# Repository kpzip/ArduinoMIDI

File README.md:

# ArduinoMIDI
program for playing MIDI files from an Arduino microcontroller automatically

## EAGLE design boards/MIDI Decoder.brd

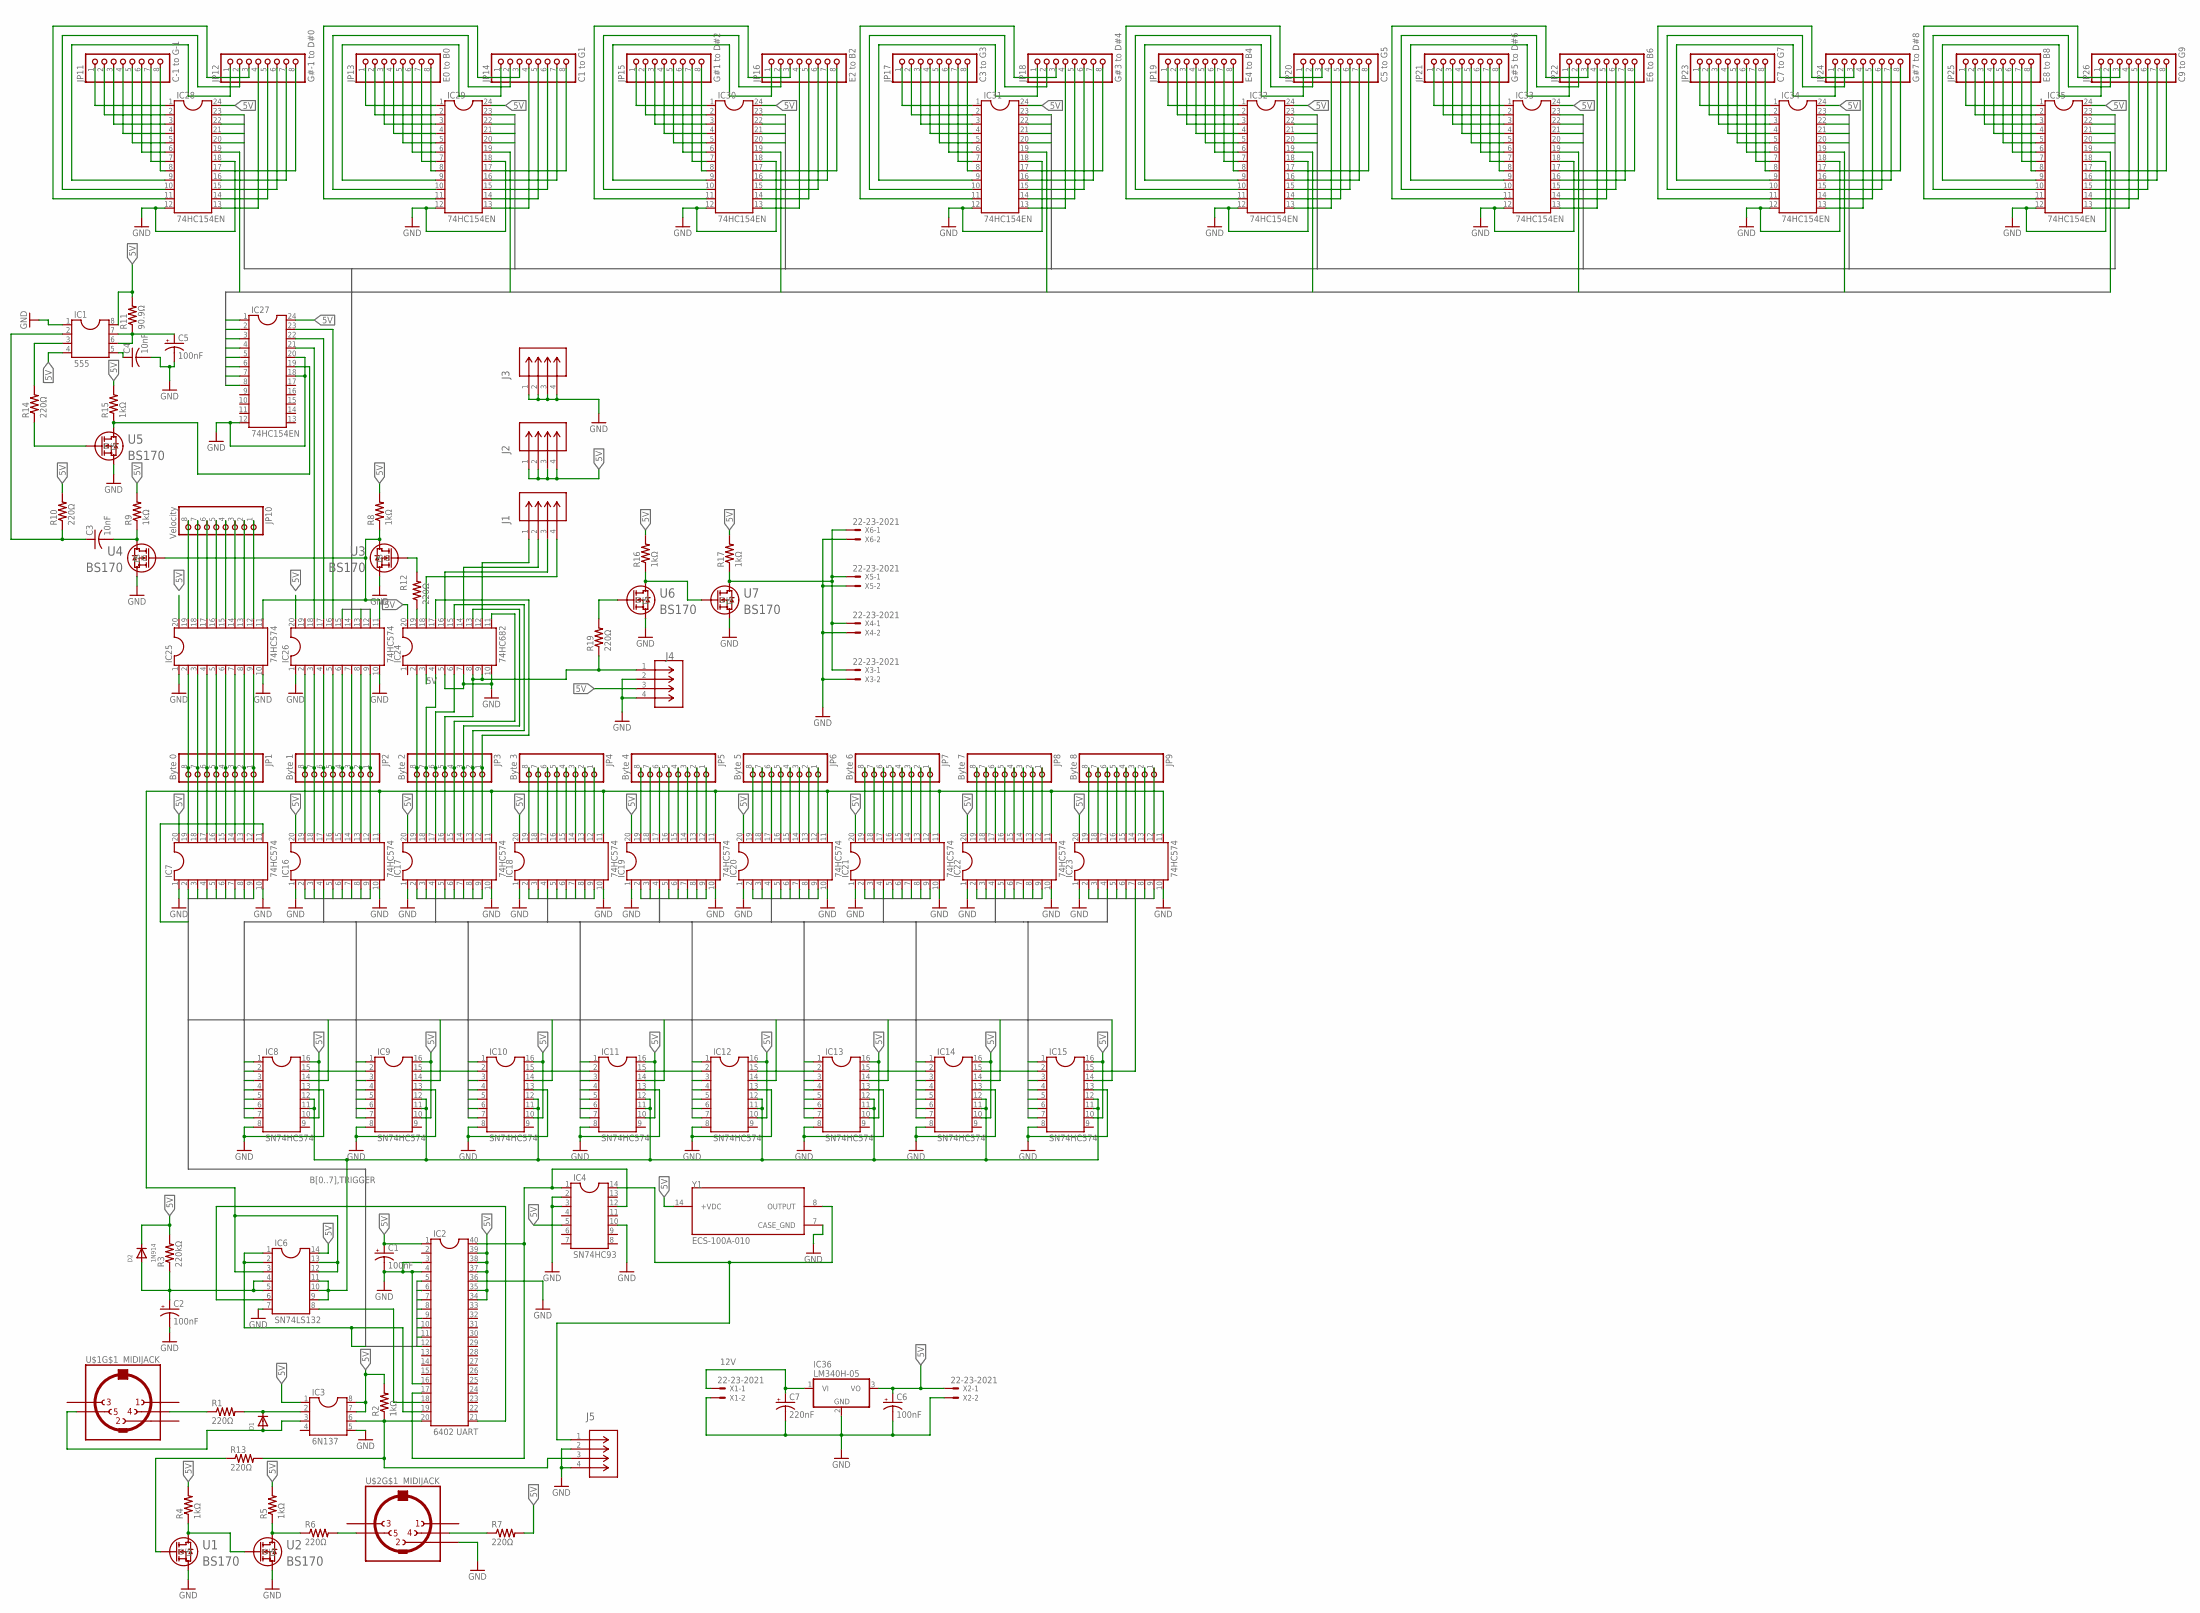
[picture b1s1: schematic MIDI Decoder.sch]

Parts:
C1, C2, C5, C6: 100nF; E1,8-4
C3, C4: 10nF; C050-025X075
C7: 220nF; E2-5
D1: DIODEDO-1N4148; DO-1N4148
D2: 1N914; DO-1N4148
IC1: 555; SOCKET-08
IC2: 6402 UART; SOCKET-40
IC3: 6N137; SOCKET-08
IC4: SN74HC93; SOCKET-14
IC6: SN74LS132; SOCKET-14
IC7, IC16, IC17, IC18, IC19, IC20, IC21, IC22, IC23, IC25, IC26: 74HC574; SOCKET-20
IC8, IC9, IC10, IC11, IC12, IC13, IC14, IC15: SN74HC574; SOCKET-16
IC24: 74HC682; SOCKET-20
IC27, IC28, IC29, IC30, IC31, IC32, IC33, IC34, IC35: 74HC154EN; SOCKET-24S
IC36: LM340H-05; TO220H
J1, J2, J3, J4, J5: 61300411121; CONN_61300411121_WRE
JP1: Byte 0; 1X08-BIG
JP2: Byte 1; 1X08-BIG
JP3: Byte 2; 1X08-BIG
JP4: Byte 3; 1X08-BIG
JP5: Byte 4; 1X08-BIG
JP6: Byte 5; 1X08-BIG
JP7: Byte 6; 1X08-BIG
JP8: Byte 7; 1X08-BIG
JP9: Byte 8; 1X08-BIG
JP10: Velocity; 1X08-BIG
JP11: C-1 to G-1; 1X08-BIG
JP12: G#-1 to D#0; 1X08-BIG
JP13: E0 to B0; 1X08-BIG
JP14: C1 to G1; 1X08-BIG
JP15: G#1 to D#2; 1X08-BIG
JP16: E2 to B2; 1X08-BIG
JP17: C3 to G3; 1X08-BIG
JP18: G#3 to D#4; 1X08-BIG
JP19: E4 to B4; 1X08-BIG
JP20: C5 to G5; 1X08-BIG
JP21: G#5 to D#6; 1X08-BIG
JP22: E6 to B6; 1X08-BIG
JP23: C7 to G7; 1X08-BIG
JP24: G#7 to D#8; 1X08-BIG
JP25: E8 to B8; 1X08-BIG
JP26: C9 to G9; 1X08-BIG
R1, R6, R7, R10, R12, R13, R14, R19: 220Ω; 0207/10
R2, R4, R5, R8, R9, R15, R16, R17: 1kΩ; 0207/10
R3: 220kΩ; 0207/10
R11: 90.9Ω; 0207/10
U1, U2, U3, U4, U5, U6, U7: BS170; TO_SA06_ONS
U$1, U$2: MIDIJACK; CP-2350
X1, X2, X3, X4, X5, X6: 22-23-2021
Y1: ECS-100A-010; OSC_ECS-100A-010

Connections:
5V: C1.+, C6.+, D2.C, IC1.4, IC1.8, IC2.1, IC2.34, IC2.35, IC2.37, IC2.38, IC2.39, IC3.1, IC3.7, IC3.8, IC4.5, IC6.14, IC7.20, IC8.10, IC8.16, IC9.10, IC9.16, IC10.10, IC10.16, IC11.10, IC11.16, IC12.10, IC12.16, IC13.10, IC13.16, IC14.10, IC14.16, IC15.10, IC15.16, IC16.20, IC17.20, IC18.20, IC19.20, IC20.20, IC21.20, IC22.20, IC23.20, IC24.3, IC24.20, IC25.20, IC26.20, IC27.24, IC28.24, IC29.24, IC30.24, IC31.24, IC32.24, IC33.24, IC34.24, IC35.24, IC36.3 (VO), J2.1, J2.2, J2.3, J2.4, J4.3, R2.2, R3.2, R4.2, R5.2, R7.2, R8.2, R9.2, R10.2, R11.2, R15.2, R16.2, R17.2, X2.1, Y1.14 (+VDC)
12V: C7.+, IC36.1 (VI), X1.1
B0: IC2.5, IC7.2, IC8.14
B1: IC2.6, IC7.3, IC9.14
B2: IC2.7, IC7.4, IC10.14
B3: IC2.8, IC7.5, IC11.14
B4: IC2.9, IC7.6, IC12.14
B5: IC2.10, IC7.7, IC13.14
B6: IC2.11, IC7.8, IC14.14
B7: IC2.12, IC7.9, IC15.14
CHS0: IC27.1, IC28.19
CHS1: IC27.2, IC29.19
CHS2: IC27.3, IC30.19
CHS3: IC27.4, IC31.19
CHS4: IC27.5, IC32.19
CHS5: IC27.6, IC33.19
CHS6: IC27.7, IC34.19
CHS7: IC27.8, IC35.19
GND: C1.-, C2.-, C4.2, C5.-, C6.-, C7.-, IC1.1, IC2.3, IC2.4, IC2.16, IC2.36, IC3.5, IC4.2, IC4.3, IC4.10, IC6.7, IC7.1, IC7.10, IC8.8, IC8.13, IC9.8, IC9.13, IC10.8, IC10.13, IC11.8, IC11.13, IC12.8, IC12.13, IC13.8, IC13.13, IC14.8, IC14.13, IC15.8, IC15.13, IC16.1, IC16.10, IC17.1, IC17.10, IC18.1, IC18.10, IC19.1, IC19.10, IC20.1, IC20.10, IC21.1, IC21.10, IC22.1, IC22.10, IC23.1, IC23.10, IC24.5, IC24.7, IC24.10, IC25.1, IC25.10, IC26.1, IC26.10, IC27.12, IC27.18, IC27.20, IC28.12, IC28.18, IC29.12, IC29.18, IC30.12, IC30.18, IC31.12, IC31.18, IC32.12, IC32.18, IC33.12, IC33.18, IC34.12, IC34.18, IC35.12, IC35.18, IC36.2 (GND), J3.1, J3.2, J3.3, J3.4, J4.2, J4.4, J5.2, J5.4, U1.3 (S), U2.3 (S), U3.3 (S), U4.3 (S), U5.3 (S), U6.3 (S), U7.3 (S), U$2.2, X1.2, X2.2, X3.2, X4.2, X5.2, X6.2, Y1.7 (CASE_GND)
unnamed: D1.A, IC3.3, U$1.5
unnamed: D1.C, IC3.2, R1.2
unnamed: IC2.20, IC3.6, J5.3, R2.1, R13.2
unnamed: R1.1, U$1.4
unnamed: IC2.17, IC2.40, IC4.1, IC4.12
unnamed: C3.1, IC1.2, R10.1
unnamed: C5.+, IC1.6, IC1.7, R11.1
unnamed: IC4.14, J5.1, Y1.8 (OUTPUT)
unnamed: IC24.19, R12.1
unnamed: R4.1, U1.1 (D), U2.2 (G)
unnamed: C4.1, IC1.5
unnamed: IC7.19, IC25.2, JP1.8
unnamed: IC2.18, IC6.8
unnamed: IC6.3, IC6.12, IC6.13, IC16.11, IC17.11, IC18.11, IC19.11, IC20.11, IC21.11, IC22.11, IC23.11
unnamed: IC1.3, R14.2
unnamed: IC2.21, IC6.6
unnamed: C2.+, D2.A, IC6.4, IC6.5, R3.1
unnamed: R14.1, U5.2 (G)
unnamed: R6.2, U$2.5
unnamed: R5.1, R6.1, U2.1 (D)
unnamed: R7.1, U$2.4
unnamed: R13.1, U1.2 (G)
unnamed: IC24.12, J1.1
unnamed: R16.1, U6.1 (D), U7.2 (G)
unnamed: IC27.19, R15.1, U5.1 (D)
unnamed: R17.1, U7.1 (D), X3.1, X4.1, X5.1, X6.1
unnamed: R19.2, U6.2 (G)
unnamed: IC6.9, IC6.10, IC6.11, IC8.11, IC8.12, IC9.11, IC9.12, IC10.11, IC10.12, IC11.11, IC11.12, IC12.11, IC12.12, IC13.11, IC13.12, IC14.11, IC14.12, IC15.11, IC15.12
unnamed: IC7.18, IC25.3, JP1.7
unnamed: IC7.17, IC25.4, JP1.6
unnamed: IC7.16, IC25.5, JP1.5
unnamed: IC7.15, IC25.6, JP1.4
unnamed: IC7.14, IC25.7, JP1.3
unnamed: IC7.13, IC25.8, JP1.2
unnamed: IC7.12, IC25.9, JP1.1
unnamed: IC16.19, IC26.2, JP2.8
unnamed: IC16.18, IC26.3, JP2.7
unnamed: IC16.17, IC26.4, JP2.6
unnamed: IC16.16, IC26.5, JP2.5
unnamed: IC16.15, IC26.6, JP2.4
unnamed: IC16.14, IC26.7, JP2.3
unnamed: IC16.13, IC26.8, JP2.2
unnamed: IC16.12, IC26.9, JP2.1
unnamed: IC24.14, J1.2
unnamed: IC24.16, J1.3
unnamed: IC24.18, J1.4
unnamed: R12.2, U3.2 (G)
unnamed: IC25.11, IC26.11, R8.1, U3.1 (D), U4.2 (G)
unnamed: IC25.19, JP10.8
unnamed: C3.2, R9.1, U4.1 (D)
unnamed: IC25.18, JP10.7
unnamed: IC18.19, JP4.8
unnamed: IC18.18, JP4.7
unnamed: IC18.17, JP4.6
unnamed: IC18.16, JP4.5
unnamed: IC18.15, JP4.4
unnamed: IC18.14, JP4.3
unnamed: IC18.13, JP4.2
unnamed: IC18.12, JP4.1
unnamed: IC19.19, JP5.8
unnamed: IC19.18, JP5.7
unnamed: IC19.17, JP5.6
unnamed: IC19.16, JP5.5
unnamed: IC19.15, JP5.4
unnamed: IC19.14, JP5.3
unnamed: IC19.13, JP5.2
unnamed: IC19.12, JP5.1
unnamed: IC20.19, JP6.8
unnamed: IC20.18, JP6.7
unnamed: IC20.17, JP6.6
unnamed: IC20.16, JP6.5
unnamed: IC20.15, JP6.4
unnamed: IC20.14, JP6.3
unnamed: IC20.13, JP6.2
unnamed: IC20.12, JP6.1
unnamed: IC21.19, JP7.8
unnamed: IC21.18, JP7.7
unnamed: IC21.17, JP7.6
unnamed: IC21.16, JP7.5
unnamed: IC21.15, JP7.4
unnamed: IC21.14, JP7.3
unnamed: IC21.13, JP7.2
unnamed: IC21.12, JP7.1
unnamed: IC22.19, JP8.8
unnamed: IC22.18, JP8.7
unnamed: IC22.17, JP8.6
unnamed: IC22.16, JP8.5
unnamed: IC22.15, JP8.4
unnamed: IC22.14, JP8.3
unnamed: IC22.13, JP8.2
unnamed: IC22.12, JP8.1
unnamed: IC23.19, JP9.8
unnamed: IC23.18, JP9.7
unnamed: IC23.17, JP9.6
unnamed: IC23.16, JP9.5
unnamed: IC23.15, JP9.4
unnamed: IC23.14, JP9.3
unnamed: IC23.13, JP9.2
unnamed: IC23.12, JP9.1
unnamed: IC25.17, JP10.6
unnamed: IC25.16, JP10.5
unnamed: IC25.15, JP10.4
unnamed: IC25.14, JP10.3
unnamed: IC25.13, JP10.2
unnamed: IC25.12, JP10.1
unnamed: IC26.18, IC27.21
unnamed: IC26.17, IC27.22
unnamed: IC26.16, IC27.23
unnamed: IC28.1, JP11.1
unnamed: IC28.2, JP11.2
unnamed: IC28.3, JP11.3
unnamed: IC28.4, JP11.4
unnamed: IC28.5, JP11.5
unnamed: IC28.6, JP11.6
unnamed: IC28.7, JP11.7
unnamed: IC28.8, JP11.8
unnamed: IC28.9, JP12.1
unnamed: IC28.10, JP12.2
unnamed: IC28.11, JP12.3
unnamed: IC28.13, JP12.4
unnamed: IC28.14, JP12.5
unnamed: IC28.15, JP12.6
unnamed: IC28.16, JP12.7
unnamed: IC28.17, JP12.8
unnamed: IC29.1, JP13.1
unnamed: IC29.2, JP13.2
unnamed: IC29.3, JP13.3
unnamed: IC29.4, JP13.4
unnamed: IC29.5, JP13.5
unnamed: IC29.6, JP13.6
unnamed: IC29.7, JP13.7
unnamed: IC29.8, JP13.8
unnamed: IC29.9, JP14.1
unnamed: IC29.10, JP14.2
unnamed: IC29.11, JP14.3
unnamed: IC29.13, JP14.4
unnamed: IC29.14, JP14.5
unnamed: IC29.15, JP14.6
unnamed: IC29.16, JP14.7
unnamed: IC29.17, JP14.8
unnamed: IC30.1, JP15.1
unnamed: IC30.2, JP15.2
unnamed: IC30.3, JP15.3
unnamed: IC30.4, JP15.4
unnamed: IC30.5, JP15.5
unnamed: IC30.6, JP15.6
unnamed: IC30.7, JP15.7
unnamed: IC30.8, JP15.8
unnamed: IC30.9, JP16.1
unnamed: IC30.10, JP16.2
unnamed: IC30.11, JP16.3
unnamed: IC30.13, JP16.4
unnamed: IC30.14, JP16.5
unnamed: IC30.15, JP16.6
unnamed: IC30.16, JP16.7
unnamed: IC30.17, JP16.8
unnamed: IC31.1, JP17.1
unnamed: IC31.2, JP17.2
unnamed: IC31.3, JP17.3
unnamed: IC31.4, JP17.4
unnamed: IC31.5, JP17.5
unnamed: IC31.6, JP17.6
unnamed: IC31.7, JP17.7
unnamed: IC31.8, JP17.8
unnamed: IC31.9, JP18.1
unnamed: IC31.10, JP18.2
unnamed: IC31.11, JP18.3
unnamed: IC31.13, JP18.4
unnamed: IC31.14, JP18.5
unnamed: IC31.15, JP18.6
unnamed: IC31.16, JP18.7
unnamed: IC31.17, JP18.8
unnamed: IC32.1, JP19.1
unnamed: IC32.2, JP19.2
unnamed: IC32.3, JP19.3
unnamed: IC32.4, JP19.4
unnamed: IC32.5, JP19.5
unnamed: IC32.6, JP19.6
unnamed: IC32.7, JP19.7
unnamed: IC32.8, JP19.8
unnamed: IC32.9, JP20.1
unnamed: IC32.10, JP20.2
unnamed: IC32.11, JP20.3
unnamed: IC32.13, JP20.4
unnamed: IC32.14, JP20.5
unnamed: IC32.15, JP20.6
unnamed: IC32.16, JP20.7
unnamed: IC32.17, JP20.8
unnamed: IC33.1, JP21.1
unnamed: IC33.2, JP21.2
unnamed: IC33.3, JP21.3
unnamed: IC33.4, JP21.4
unnamed: IC33.5, JP21.5
unnamed: IC33.6, JP21.6
unnamed: IC33.7, JP21.7
unnamed: IC33.8, JP21.8
unnamed: IC33.9, JP22.1
unnamed: IC33.10, JP22.2
unnamed: IC33.11, JP22.3
unnamed: IC33.13, JP22.4
unnamed: IC33.14, JP22.5
unnamed: IC33.15, JP22.6
unnamed: IC33.16, JP22.7
unnamed: IC33.17, JP22.8
unnamed: IC34.1, JP23.1
unnamed: IC34.2, JP23.2
unnamed: IC34.3, JP23.3
unnamed: IC34.4, JP23.4
unnamed: IC34.5, JP23.5
unnamed: IC34.6, JP23.6
unnamed: IC34.7, JP23.7
unnamed: IC34.8, JP23.8
unnamed: IC34.9, JP24.1
unnamed: IC34.10, JP24.2
unnamed: IC34.11, JP24.3
unnamed: IC34.13, JP24.4
unnamed: IC34.14, JP24.5
unnamed: IC34.15, JP24.6
unnamed: IC34.16, JP24.7
unnamed: IC34.17, JP24.8
unnamed: IC35.1, JP25.1
unnamed: IC35.2, JP25.2
unnamed: IC35.3, JP25.3
unnamed: IC35.4, JP25.4
unnamed: IC35.5, JP25.5
unnamed: IC35.6, JP25.6
unnamed: IC35.7, JP25.7
unnamed: IC35.8, JP25.8
unnamed: IC35.9, JP26.1
unnamed: IC35.10, JP26.2
unnamed: IC35.11, JP26.3
unnamed: IC35.13, JP26.4
unnamed: IC35.14, JP26.5
unnamed: IC35.15, JP26.6
unnamed: IC35.16, JP26.7
unnamed: IC35.17, JP26.8
P0: IC17.19, IC24.2, JP3.8
P1: IC17.18, IC24.4, JP3.7
P2: IC17.17, IC24.6, JP3.6
P3: IC17.16, IC24.8, IC24.9, J4.1, JP3.5, R19.1
P4: IC17.15, IC24.11, JP3.4
P5: IC17.14, IC24.13, JP3.3
P6: IC17.13, IC24.15, JP3.2
P7: IC17.12, IC24.17, JP3.1
S0: IC26.12, IC28.23, IC29.23, IC30.23, IC31.23, IC32.23, IC33.23, IC34.23, IC35.23
S1: IC26.13, IC28.22, IC29.22, IC30.22, IC31.22, IC32.22, IC33.22, IC34.22, IC35.22
S2: IC26.14, IC28.21, IC29.21, IC30.21, IC31.21, IC32.21, IC33.21, IC34.21, IC35.21
S3: IC26.15, IC28.20, IC29.20, IC30.20, IC31.20, IC32.20, IC33.20, IC34.20, IC35.20
T-1-0: IC8.15, IC16.2
T-1-1: IC9.15, IC16.3
T-1-2: IC10.15, IC16.4
T-1-3: IC11.15, IC16.5
T-1-4: IC12.15, IC16.6
T-1-5: IC13.15, IC16.7
T-1-6: IC14.15, IC16.8
T-1-7: IC15.15, IC16.9
T-2-0: IC8.1, IC17.2
T-2-1: IC9.1, IC17.3
T-2-2: IC10.1, IC17.4
T-2-3: IC11.1, IC17.5
T-2-4: IC12.1, IC17.6
T-2-5: IC13.1, IC17.7
T-2-6: IC14.1, IC17.8
T-2-7: IC15.1, IC17.9
T-3-0: IC8.2, IC18.2
T-3-1: IC9.2, IC18.3
T-3-2: IC10.2, IC18.4
T-3-3: IC11.2, IC18.5
T-3-4: IC12.2, IC18.6
T-3-5: IC13.2, IC18.7
T-3-6: IC14.2, IC18.8
T-3-7: IC15.2, IC18.9
T-4-0: IC8.3, IC19.2
T-4-1: IC9.3, IC19.3
T-4-2: IC10.3, IC19.4
T-4-3: IC11.3, IC19.5
T-4-4: IC12.3, IC19.6
T-4-5: IC13.3, IC19.7
T-4-6: IC14.3, IC19.8
T-4-7: IC15.3, IC19.9
T-5-0: IC8.4, IC20.2
T-5-1: IC9.4, IC20.3
T-5-2: IC10.4, IC20.4
T-5-3: IC11.4, IC20.5
T-5-4: IC12.4, IC20.6
T-5-5: IC13.4, IC20.7
T-5-6: IC14.4, IC20.8
T-5-7: IC15.4, IC20.9
T-6-0: IC8.5, IC21.2
T-6-1: IC9.5, IC21.3
T-6-2: IC10.5, IC21.4
T-6-3: IC11.5, IC21.5
T-6-4: IC12.5, IC21.6
T-6-5: IC13.5, IC21.7
T-6-6: IC14.5, IC21.8
T-6-7: IC15.5, IC21.9
T-7-0: IC8.6, IC22.2
T-7-1: IC9.6, IC22.3
T-7-2: IC10.6, IC22.4
T-7-3: IC11.6, IC22.5
T-7-4: IC12.6, IC22.6
T-7-5: IC13.6, IC22.7
T-7-6: IC14.6, IC22.8
T-7-7: IC15.6, IC22.9
T-8-0: IC8.7, IC23.2
T-8-1: IC9.7, IC23.3
T-8-2: IC10.7, IC23.4
T-8-3: IC11.7, IC23.5
T-8-4: IC12.7, IC23.6
T-8-5: IC13.7, IC23.7
T-8-6: IC14.7, IC23.8
T-8-7: IC15.7, IC23.9
TRIGGER: IC2.19, IC6.1, IC6.2, IC7.11

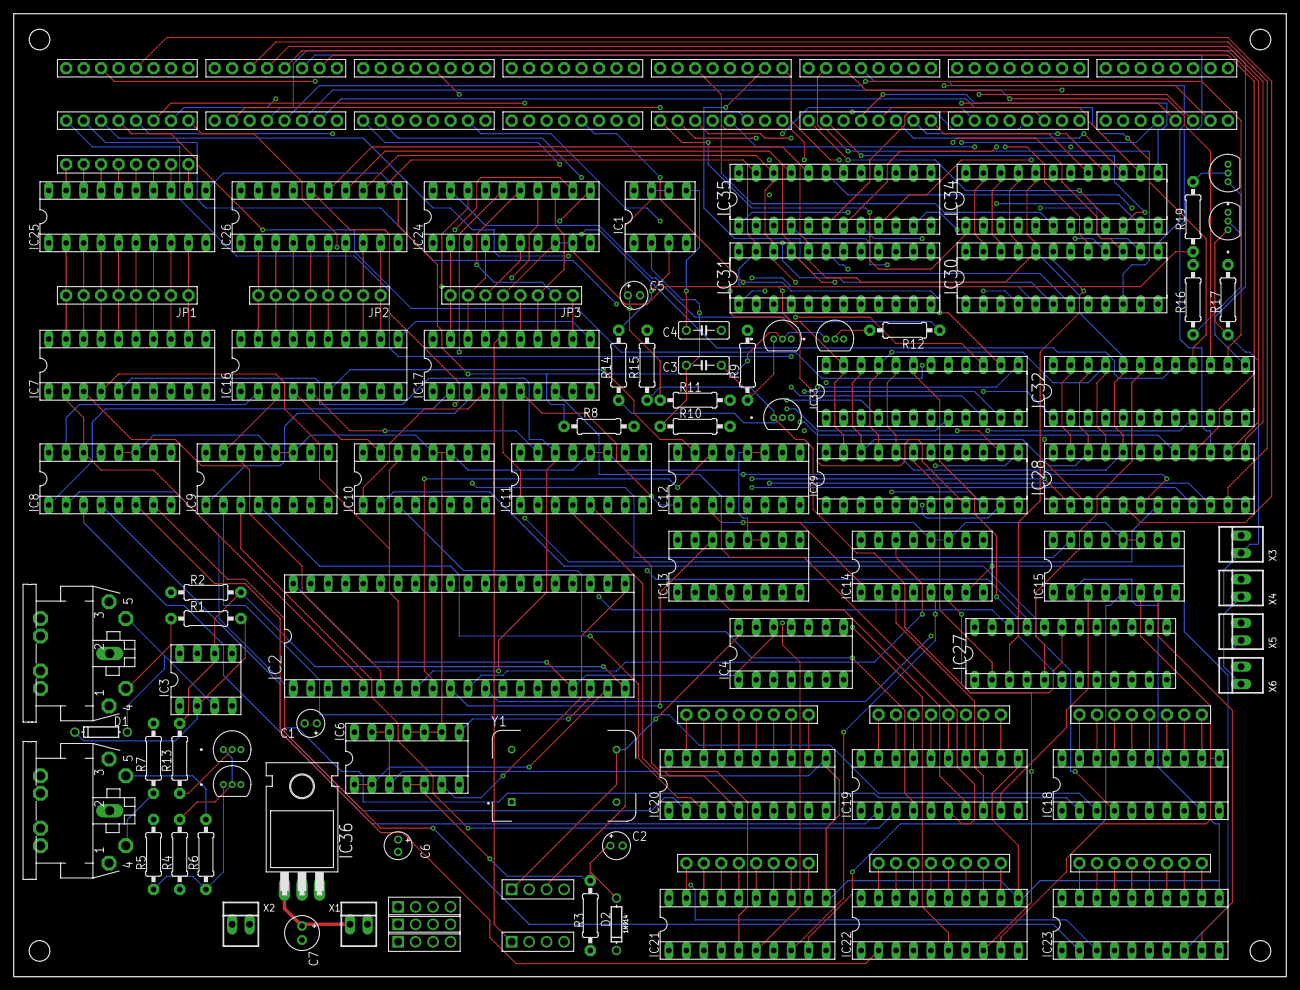
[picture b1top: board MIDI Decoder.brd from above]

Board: 6 copper layers, 185.0 x 140.0 mm, 109 parts (0 on the bottom side), 332 nets.

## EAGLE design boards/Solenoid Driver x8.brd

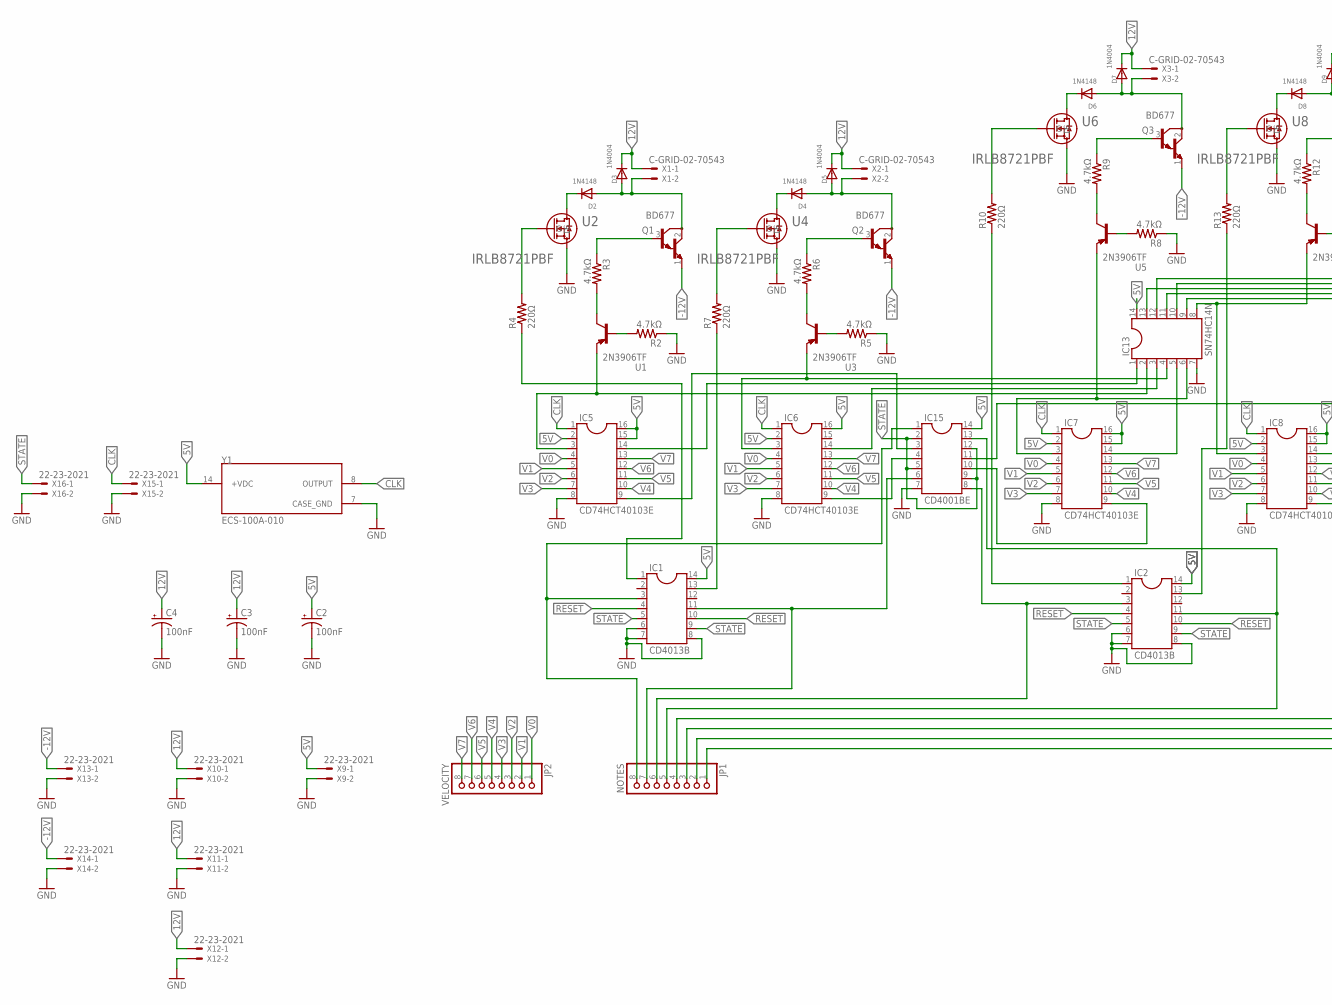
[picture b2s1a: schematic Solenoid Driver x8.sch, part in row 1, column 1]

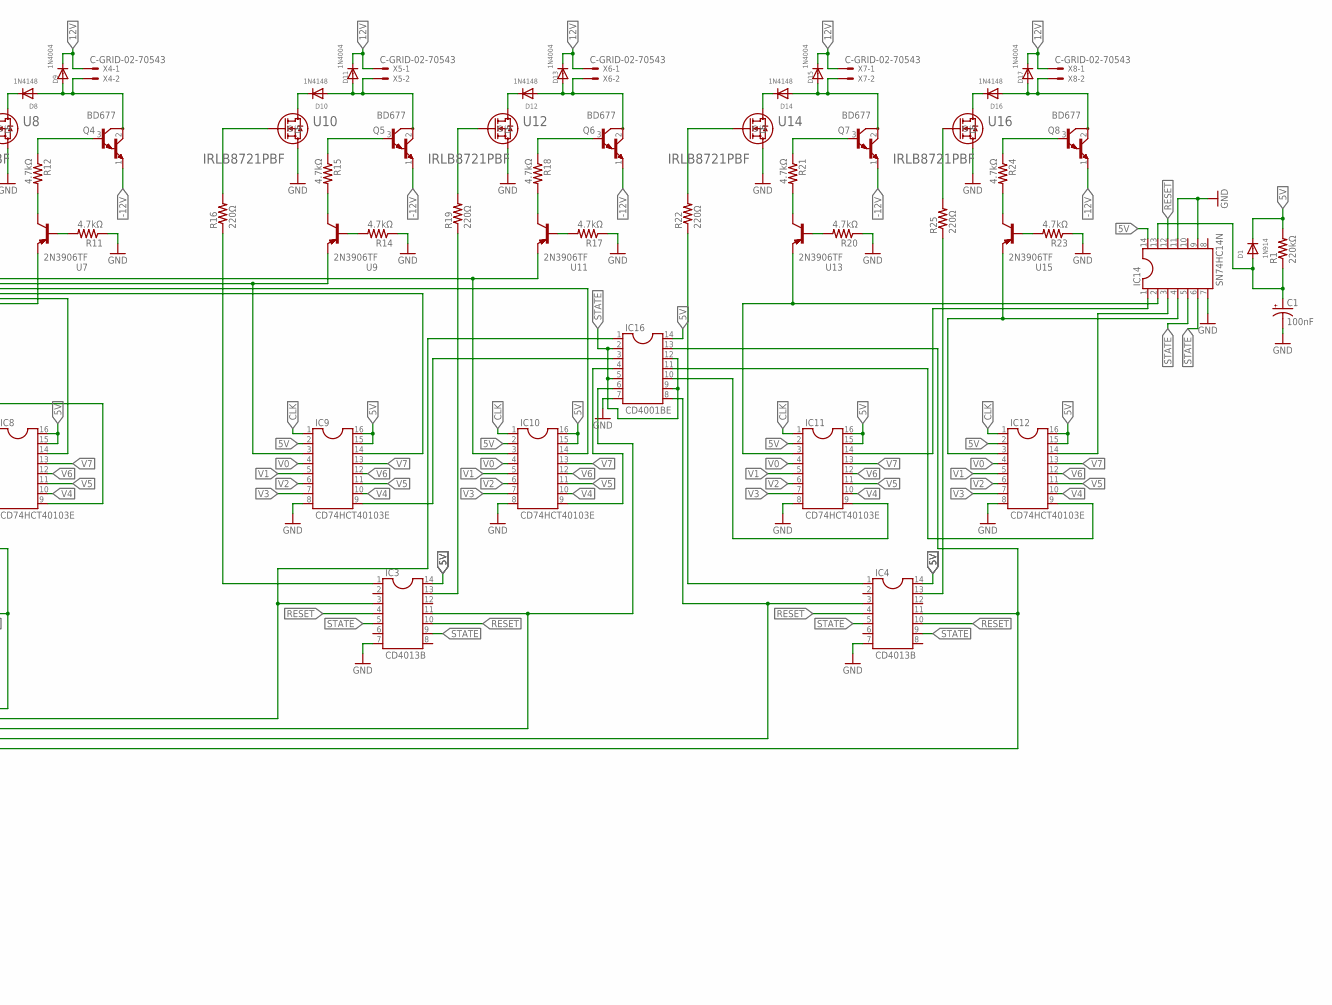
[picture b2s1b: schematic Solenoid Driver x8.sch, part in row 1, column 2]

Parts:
C1, C2, C3, C4: 100nF; E1,8-4
D1: 1N914; DO-1N4148
D2, D4, D6, D8, D10, D12, D14, D16: 1N4148; DO-1N4148
D3, D5, D7, D9, D11, D13, D15, D17: 1N4004; DO-1N4148
IC1, IC2, IC3, IC4: CD4013B; SOCKET-14
IC5, IC6, IC7, IC8, IC9, IC10, IC11, IC12: CD74HCT40103E; SOCKET-16
IC13, IC14: SN74HC14N; SOCKET-14
IC15, IC16: CD4001BE; SOCKET-14
JP1: NOTES; 1X08-BIG
JP2: VELOCITY; 1X08-BIG
Q1, Q2, Q3, Q4, Q5, Q6, Q7, Q8: BD677; TO126
R1: 220kΩ; 0207/10
R2, R3, R5, R6, R8, R9, R11, R12, R14, R15, R17, R18, R20, R21, R23, R24: 4.7kΩ; 0207/10
R4, R7, R10, R13, R16, R19, R22, R25: 220Ω; 0207/10
U1, U3, U5, U7, U9, U11, U13, U15: 2N3906TF; TO-92-3L_5P33X5P2_ONS
U2, U4, U6, U8, U10, U12, U14, U16: IRLB8721PBF; PG-TO220-3_INF
X1, X2, X3, X4, X5, X6, X7, X8: C-GRID-02-70543; 70543-02
X9, X10, X11, X12, X13, X14, X15, X16: 22-23-2021
Y1: ECS-100A-010; OSC_ECS-100A-010

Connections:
5V: C2.+, D1.C, IC1.14, IC2.14, IC3.14, IC4.14, IC5.2, IC5.15, IC5.16, IC6.2, IC6.16, IC7.2, IC7.15, IC7.16, IC8.2, IC8.15, IC8.16, IC9.2, IC9.15, IC9.16, IC10.2, IC10.15, IC10.16, IC11.2, IC11.15, IC11.16, IC12.2, IC12.15, IC12.16, IC13.14, IC14.14, IC15.14, IC16.14, R1.2, X9.1, Y1.14 (+VDC)
12V: C3.+, C4.+, D3.C, D5.C, D7.C, D9.C, D11.C, D13.C, D15.C, D17.C, X1.1, X2.1, X3.1, X4.1, X5.1, X6.1, X7.1, X8.1, X10.1, X11.1, X12.1
!STATE: IC14.6, IC15.2, IC15.5, IC15.9, IC15.12, IC16.2, IC16.5, IC16.9, IC16.12
-12V: Q1.1 (E), Q2.1 (E), Q3.1 (E), Q4.1 (E), Q5.1 (E), Q6.1 (E), Q7.1 (E), Q8.1 (E), X13.1, X14.1
CLK: IC5.1, IC6.1, IC7.1, IC8.1, IC9.1, IC10.1, IC11.1, IC12.1, X15.1, Y1.8 (OUTPUT)
GND: C1.-, C2.-, C3.-, C4.-, IC1.6, IC1.7, IC1.8, IC2.6, IC2.7, IC2.8, IC3.7, IC4.7, IC5.8, IC6.8, IC7.8, IC8.8, IC9.8, IC10.8, IC11.8, IC12.8, IC13.7, IC14.7, IC14.9, IC14.11, IC15.7, IC16.7, R2.1, R5.1, R8.1, R11.1, R14.1, R17.1, R20.1, R23.1, U2.3 (S), U4.3 (S), U6.3 (S), U8.3 (S), U10.3 (S), U12.3 (S), U14.3 (S), U16.3 (S), X9.2, X10.2, X11.2, X12.2, X13.2, X14.2, X15.2, X16.2, Y1.7 (CASE_GND)
unnamed: IC1.3, IC15.1, JP1.8
unnamed: IC5.14, IC13.1
unnamed: IC2.3, IC15.8, JP1.6
unnamed: IC2.11, IC15.13, JP1.5
unnamed: IC9.9, IC16.3
unnamed: IC3.11, IC16.6, JP1.3
unnamed: IC4.3, IC16.8, JP1.2
unnamed: IC4.11, IC16.13, JP1.1
unnamed: IC5.9, IC15.3
unnamed: IC1.1, R4.1
unnamed: IC5.3, IC13.2, U1.1 (E)
unnamed: Q1.3 (B), R3.1
unnamed: R3.2, U1.3 (C)
unnamed: R2.2, U1.2 (B)
unnamed: IC6.3, IC13.4, U3.1 (E)
unnamed: D2.A, D3.A, Q1.2 (C), X1.2
unnamed: D2.C, U2.2 (D)
unnamed: IC1.11, IC15.6, JP1.7
unnamed: C1.+, D1.A, IC14.13, R1.1
unnamed: R4.2, U2.1 (G)
unnamed: IC6.9, IC15.4
unnamed: IC11.9, IC16.10
unnamed: IC6.14, IC13.3
unnamed: IC2.13, R13.1
unnamed: Q2.3 (B), R6.1
unnamed: IC12.9, IC16.11
unnamed: IC8.14, IC13.9
unnamed: IC7.14, IC13.5
unnamed: R6.2, U3.3 (C)
unnamed: IC3.3, IC16.1, JP1.4
unnamed: IC3.1, R16.1
unnamed: R5.2, U3.2 (B)
unnamed: D4.A, D5.A, Q2.2 (C), X2.2
unnamed: R7.2, U4.1 (G)
unnamed: D4.C, U4.2 (D)
unnamed: IC4.1, R22.1
unnamed: IC1.13, R7.1
unnamed: IC12.14, IC14.3
unnamed: IC11.14, IC14.1
unnamed: Q5.3 (B), R15.1
unnamed: IC9.14, IC13.11
unnamed: IC10.14, IC13.13
unnamed: Q3.3 (B), R9.1
unnamed: R9.2, U5.3 (C)
unnamed: R8.2, U5.2 (B)
unnamed: D6.A, D7.A, Q3.2 (C), X3.2
unnamed: R10.2, U6.1 (G)
unnamed: D6.C, U6.2 (D)
unnamed: IC7.3, IC13.6, U5.1 (E)
unnamed: Q4.3 (B), R12.1
unnamed: R12.2, U7.3 (C)
unnamed: R11.2, U7.2 (B)
unnamed: D8.A, D9.A, Q4.2 (C), X4.2
unnamed: R13.2, U8.1 (G)
unnamed: D8.C, U8.2 (D)
unnamed: IC8.3, IC13.8, U7.1 (E)
unnamed: R15.2, U9.3 (C)
unnamed: IC2.1, R10.1
unnamed: R14.2, U9.2 (B)
unnamed: D10.A, D11.A, Q5.2 (C), X5.2
unnamed: R16.2, U10.1 (G)
unnamed: D10.C, U10.2 (D)
unnamed: Q6.3 (B), R18.1
unnamed: R18.2, U11.3 (C)
unnamed: R17.2, U11.2 (B)
unnamed: D12.A, D13.A, Q6.2 (C), X6.2
unnamed: R19.2, U12.1 (G)
unnamed: D12.C, U12.2 (D)
unnamed: IC10.3, IC13.12, U11.1 (E)
unnamed: IC7.9, IC15.10
unnamed: IC3.13, R19.1
unnamed: Q7.3 (B), R21.1
unnamed: R21.2, U13.3 (C)
unnamed: R20.2, U13.2 (B)
unnamed: D14.A, D15.A, Q7.2 (C), X7.2
unnamed: R22.2, U14.1 (G)
unnamed: D14.C, U14.2 (D)
unnamed: IC11.3, IC14.2, U13.1 (E)
unnamed: Q8.3 (B), R24.1
unnamed: R24.2, U15.3 (C)
unnamed: R23.2, U15.2 (B)
unnamed: D16.A, D17.A, Q8.2 (C), X8.2
unnamed: R25.2, U16.1 (G)
unnamed: D16.C, U16.2 (D)
unnamed: IC12.3, IC14.4, U15.1 (E)
unnamed: IC4.13, R25.1
unnamed: IC8.9, IC15.11
unnamed: IC10.9, IC16.4
unnamed: IC9.3, IC13.10, U9.1 (E)
RESET: IC1.4, IC1.10, IC2.4, IC2.10, IC3.4, IC3.10, IC4.4, IC4.10, IC14.12
STATE: IC1.5, IC1.9, IC2.5, IC2.9, IC3.5, IC3.9, IC4.5, IC4.9, IC14.5, X16.1
V0: IC5.4, IC6.4, IC7.4, IC8.4, IC9.4, IC10.4, IC11.4, IC12.4, JP2.1
V1: IC5.5, IC6.5, IC7.5, IC8.5, IC9.5, IC10.5, IC11.5, IC12.5, JP2.2
V2: IC5.6, IC6.6, IC7.6, IC8.6, IC9.6, IC10.6, IC11.6, IC12.6, JP2.3
V3: IC5.7, IC6.7, IC7.7, IC8.7, IC9.7, IC10.7, IC11.7, IC12.7, JP2.4
V4: IC5.10, IC6.10, IC7.10, IC8.10, IC9.10, IC10.10, IC11.10, IC12.10, JP2.5
V5: IC5.11, IC6.11, IC7.11, IC8.11, IC9.11, IC10.11, IC11.11, IC12.11, JP2.6
V6: IC5.12, IC6.12, IC7.12, IC8.12, IC9.12, IC10.12, IC11.12, IC12.12, JP2.7
V7: IC5.13, IC6.13, IC7.13, IC8.13, IC9.13, IC10.13, IC11.13, IC12.13, JP2.8

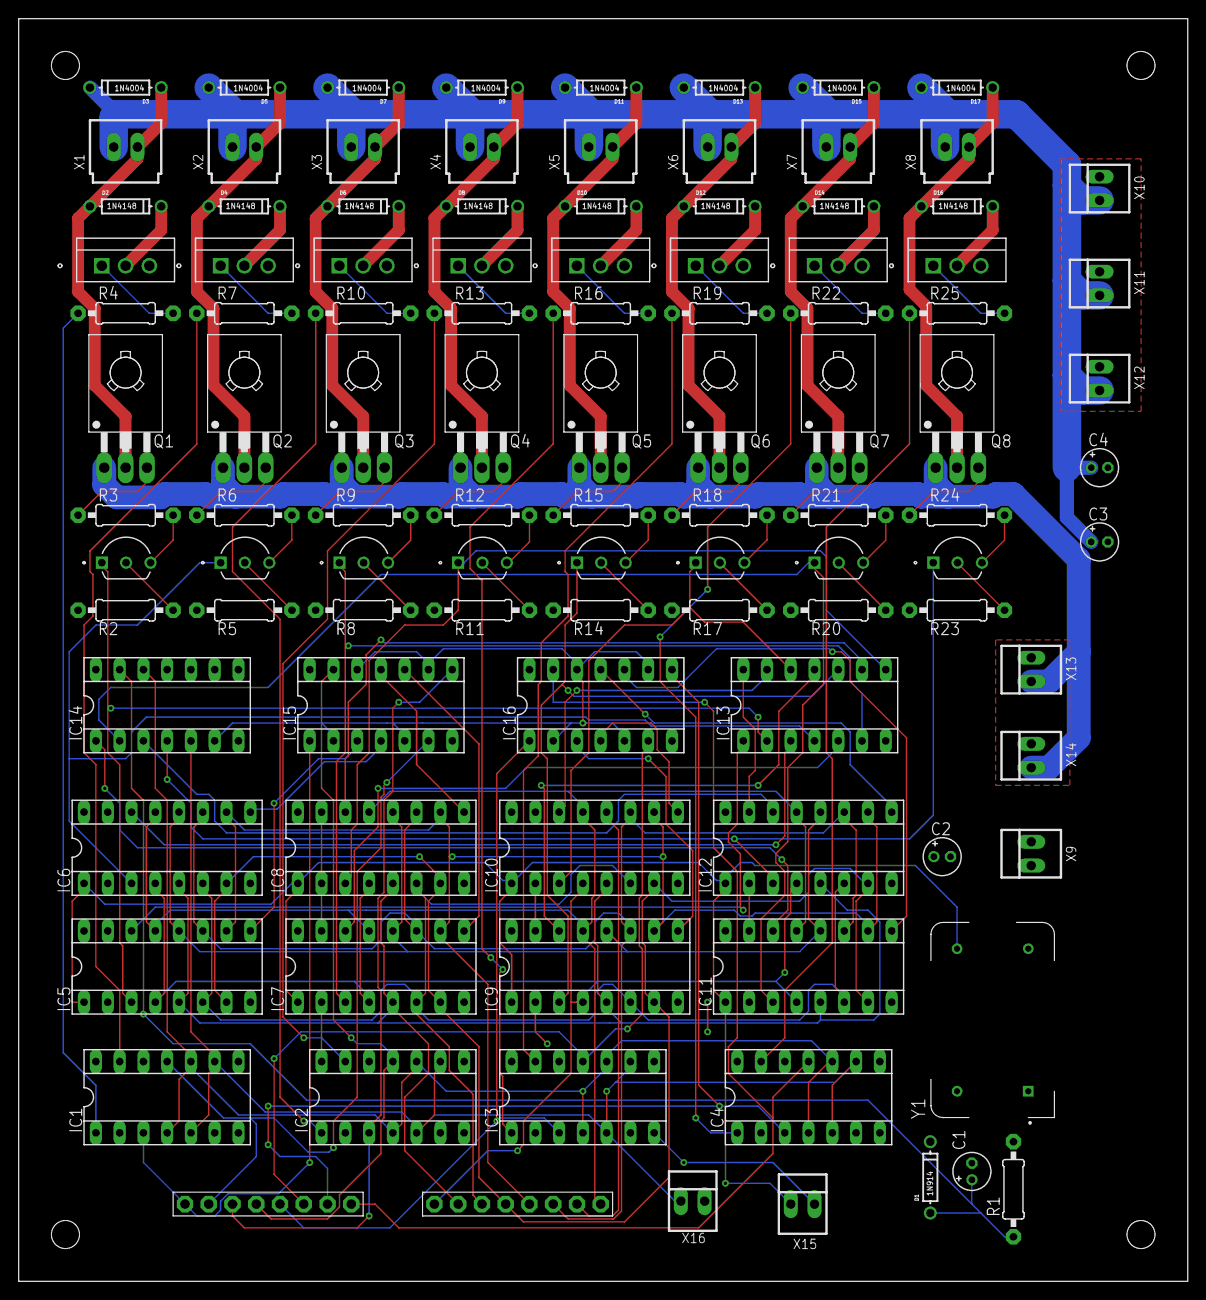
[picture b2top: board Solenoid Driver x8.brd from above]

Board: 2 copper layers, 125.0 x 135.0 mm, 105 parts (0 on the bottom side), 105 nets.

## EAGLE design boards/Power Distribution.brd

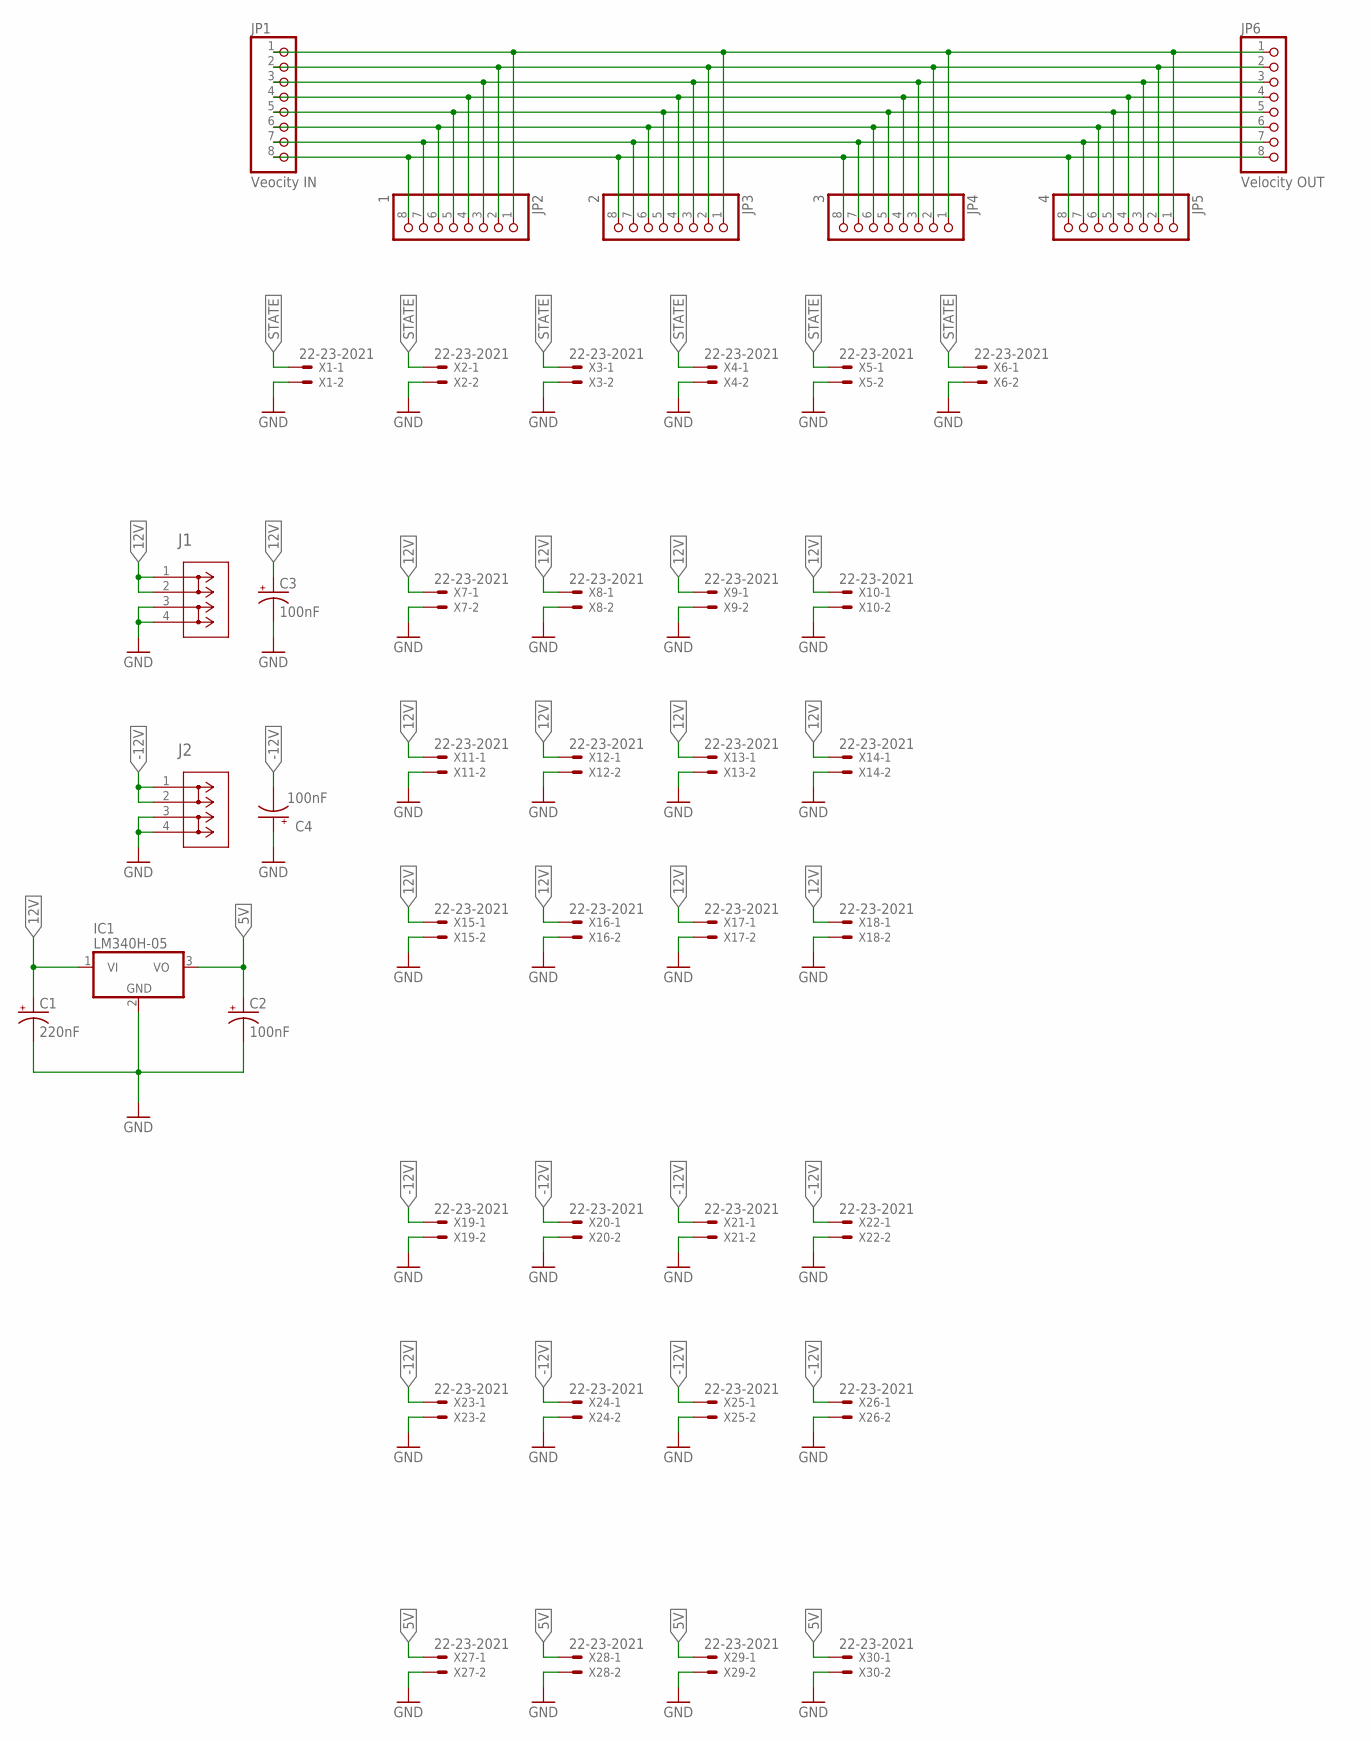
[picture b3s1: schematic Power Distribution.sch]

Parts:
C1: 220nF; E2-5
C2, C3, C4: 100nF; E1,8-4
IC1: LM340H-05; TO220H
J1, J2: 691256610002; CONN_691256610002_WRE
JP1: Veocity IN; 1X08-BIG
JP2: 1; 1X08-BIG
JP3: 2; 1X08-BIG
JP4: 3; 1X08-BIG
JP5: 4; 1X08-BIG
JP6: Velocity OUT; 1X08-BIG
X1, X2, X3, X4, X5, X6, X7, X8, X9, X10, X11, X12, X13, X14, X15, X16, X17, X18, X19, X20, X21, X22, X23, X24, X25, X26, X27, X28, X29, X30: 22-23-2021

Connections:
5V: C2.+, IC1.3 (VO), X27.1, X28.1, X29.1, X30.1
12V: C1.+, C3.+, IC1.1 (VI), J1.1, J1.2, X7.1, X8.1, X9.1, X10.1, X11.1, X12.1, X13.1, X14.1, X15.1, X16.1, X17.1, X18.1
-12V: C4.-, J2.1, J2.2, X19.1, X20.1, X21.1, X22.1, X23.1, X24.1, X25.1, X26.1
GND: C1.-, C2.-, C3.-, C4.+, IC1.2 (GND), J1.3, J1.4, J2.3, J2.4, X1.2, X2.2, X3.2, X4.2, X5.2, X6.2, X7.2, X8.2, X9.2, X10.2, X11.2, X12.2, X13.2, X14.2, X15.2, X16.2, X17.2, X18.2, X19.2, X20.2, X21.2, X22.2, X23.2, X24.2, X25.2, X26.2, X27.2, X28.2, X29.2, X30.2
unnamed: JP1.1, JP2.1, JP3.1, JP4.1, JP5.1, JP6.1
unnamed: JP1.2, JP2.2, JP3.2, JP4.2, JP5.2, JP6.2
unnamed: JP1.3, JP2.3, JP3.3, JP4.3, JP5.3, JP6.3
unnamed: JP1.4, JP2.4, JP3.4, JP4.4, JP5.4, JP6.4
unnamed: JP1.5, JP2.5, JP3.5, JP4.5, JP5.5, JP6.5
unnamed: JP1.6, JP2.6, JP3.6, JP4.6, JP5.6, JP6.6
unnamed: JP1.7, JP2.7, JP3.7, JP4.7, JP5.7, JP6.7
unnamed: JP1.8, JP2.8, JP3.8, JP4.8, JP5.8, JP6.8
STATE: X1.1, X2.1, X3.1, X4.1, X5.1, X6.1

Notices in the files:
parts and their libraries:
COPYRIGHT: Copyright (C) 2024 Ultra Librarian. All rights reserved.
